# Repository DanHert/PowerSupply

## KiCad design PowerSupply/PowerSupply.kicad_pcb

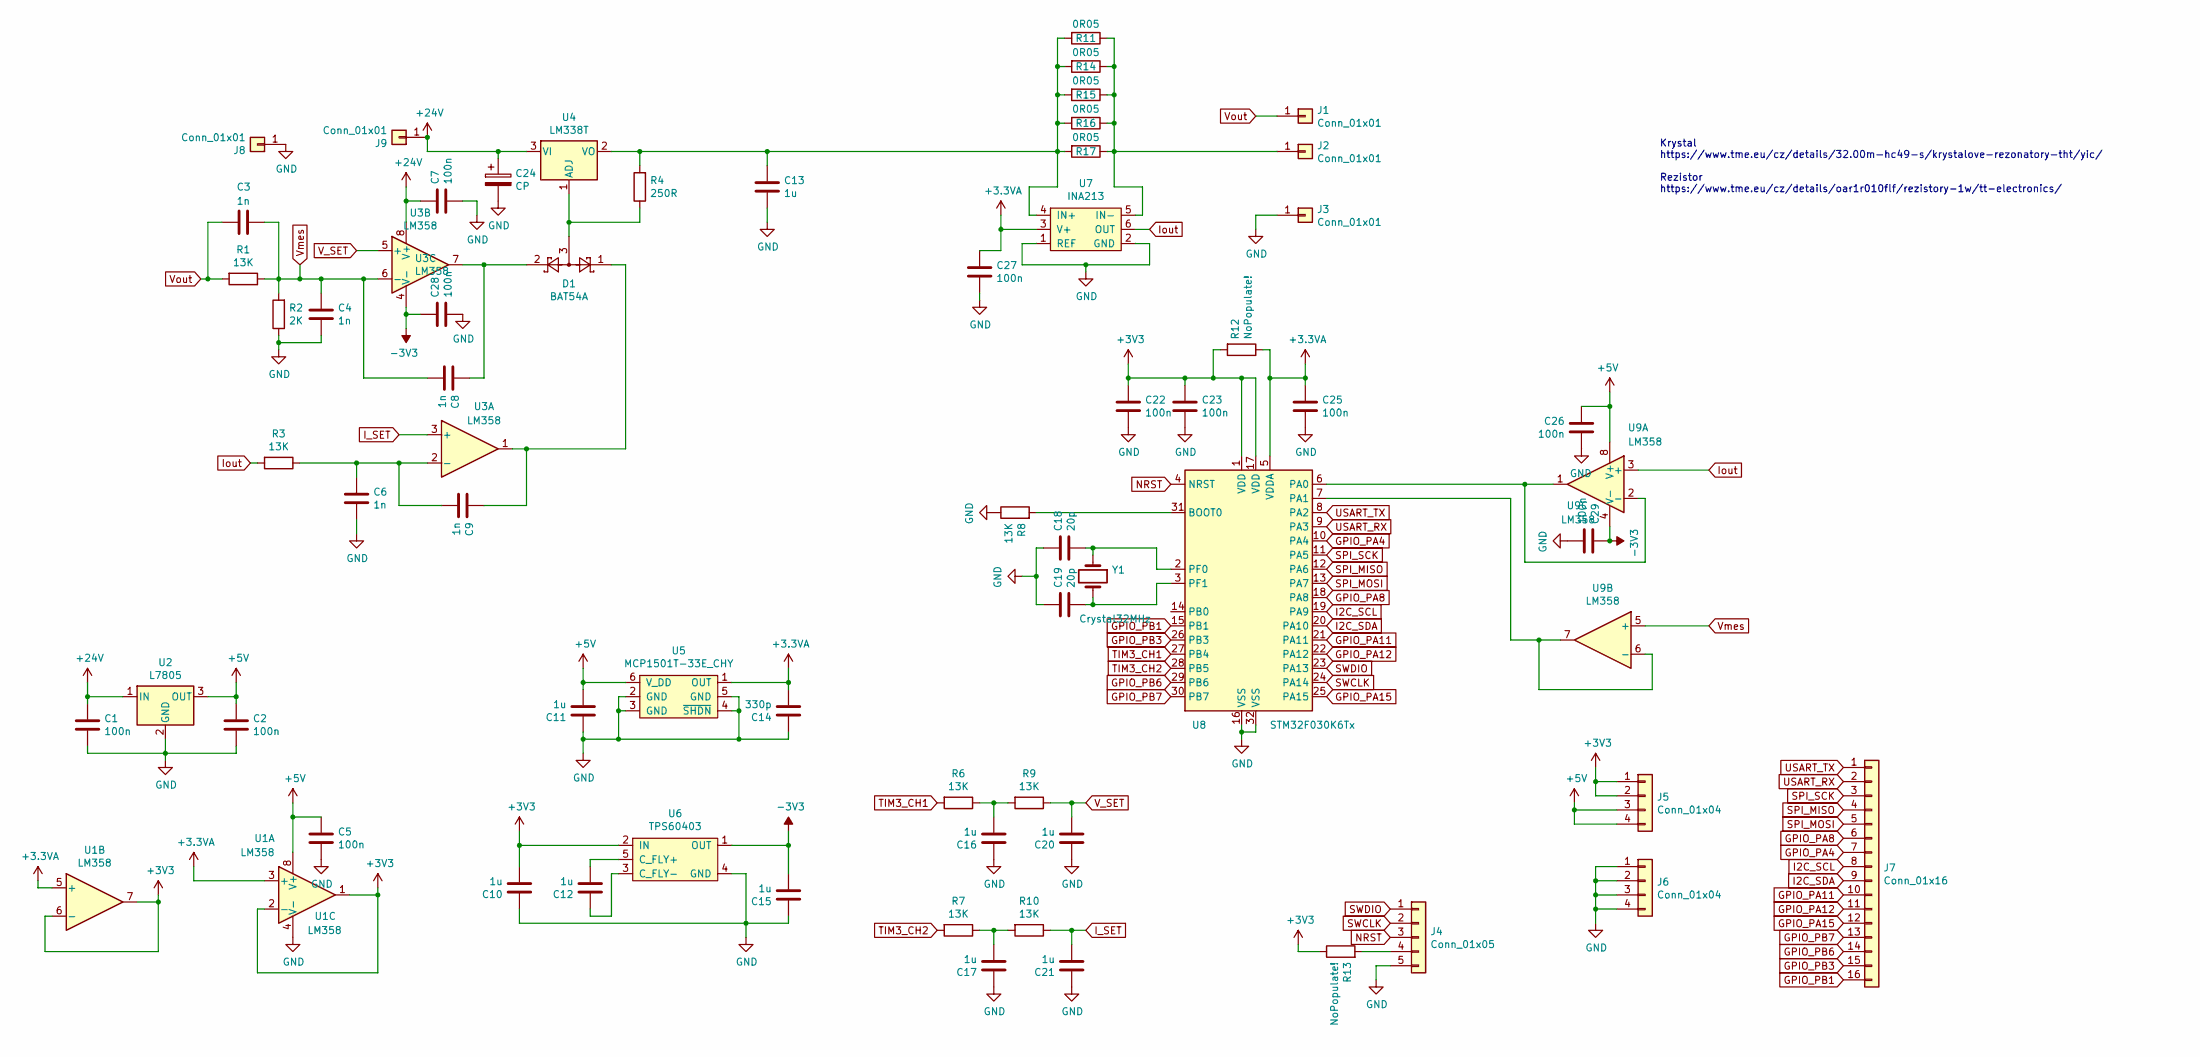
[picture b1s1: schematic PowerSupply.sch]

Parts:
C1, C2, C5, C7, C22, C23, C25, C26, C27, C28, C29: 100n; C_0805_2012Metric
C3, C4, C6, C8, C9: 1n; C_0805_2012Metric
C10, C11, C12, C13, C15, C16, C17, C20, C21: 1u; C_0805_2012Metric
C14: 330p; C_0805_2012Metric
C18, C19: 20p; C_0805_2012Metric
C24: CP; CP_Radial_D6.3mm_P2.50mm
D1: BAT54A; SOT-23
J1: Conn_01x01; SolderWirePad_1x01_Drill0.8mm
J2, J3, J8, J9: Conn_01x01; SolderWirePad_1x01_Drill2mm
J4: Conn_01x05; PinHeader_1x05_P2.54mm_Vertical
J5, J6: Conn_01x04; PinSocket_1x04_P2.54mm_Vertical
J7: Conn_01x16; PinSocket_1x16_P2.54mm_Vertical
R1, R3, R6, R7, R8, R9, R10: 13K; R_0805_2012Metric
R2: 2K; R_0805_2012Metric
R4: 250R; R_0805_2012Metric
R11, R14, R15, R16, R17: 0R05; R_1206_3216Metric
R12, R13: NoPopulate!; R_0805_2012Metric
U1, U3, U9: LM358; SOIC-8_3.9x4.9mm_P1.27mm
U2: L7805; TO-252-2
U4: LM338T; TO-220-3_Vertical
U5: MCP1501T-33E_CHY; SOT-23-6
U6: TPS60403; SOT-23-5
U7: INA213; SOT-363_SC-70-6_Handsoldering
U8: STM32F030K6Tx; LQFP-32_7x7mm_P0.8mm
Y1: Crystal32MHz; Crystal_HC49-U_Vertical

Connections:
+3.3VA: C14.2, C25.1, C27.1, R12.1, U1.3 (+), U1.5 (+), U5.1 (OUT), U7.3 (V+), U8.5 (VDDA)
+3V3: C10.2, C22.1, C23.1, J5.1, J5.2, R12.2, R13.1, U1.1, U1.2 (-), U1.6 (-), U1.7, U6.2 (IN), U8.1 (VDD), U8.17 (VDD)
+5V: C2.1, C5.1, C11.2, C26.1, J5.3, J5.4, U1.8 (V+), U2.3 (OUT), U5.6 (V_DD), U9.8 (V+)
+24V: C1.1, C7.1, C24.1, J9.1, U2.1 (IN), U3.8 (V+), U4.3 (VI)
-3V3: C15.2, C28.1, C29.1, U3.4 (V-), U6.1 (OUT), U9.4 (V-)
GND: C1.2, C2.2, C4.2, C5.2, C6.2, C7.2, C10.1, C11.1, C13.2, C14.1, C15.1, C16.1, C17.1, C18.1, C19.1, C20.1, C21.1, C22.2, C23.2, C24.2, C25.2, C26.2, C27.2, C28.2, C29.2, J3.1, J4.5, J6.1, J6.2, J6.3, J6.4, J8.1, R2.1, R8.1, U1.4 (V-), U2.2 (GND), U5.2 (GND), U5.3 (GND), U5.4 (~SHDN), U5.5 (GND), U6.4 (GND), U7.1 (REF), U7.2 (GND), U8.16 (VSS), U8.32 (VSS)
GPIO_PA4: J7.7, U8.10 (PA4)
GPIO_PA8: J7.6, U8.18 (PA8)
GPIO_PA11: J7.10, U8.21 (PA11)
GPIO_PA12: J7.11, U8.22 (PA12)
GPIO_PA15: J7.12, U8.25 (PA15)
GPIO_PB1: J7.16, U8.15 (PB1)
GPIO_PB3: J7.15, U8.26 (PB3)
GPIO_PB6: J7.14, U8.29 (PB6)
GPIO_PB7: J7.13, U8.30 (PB7)
I2C_SCL: J7.8, U8.19 (PA9)
I2C_SDA: J7.9, U8.20 (PA10)
I_SET: C21.2, R10.1, U3.3 (+)
Iout: R3.2, U7.6 (OUT), U9.3 (+)
NRST: J4.3, U8.4 (NRST)
unnamed: C6.1, C9.2, R3.1, U3.2 (-)
unnamed: C8.1, D1.2, U3.7
unnamed: C9.1, D1.1, U3.1
unnamed: C12.1, U6.3 (C_FLY-)
unnamed: C12.2, U6.5 (C_FLY+)
unnamed: C13.1, R4.2, R11.2, R14.2, R15.2, R16.2, R17.2, U4.2 (VO), U7.4 (IN+)
unnamed: C16.2, R6.1, R9.2
unnamed: C17.2, R7.1, R10.2
unnamed: C18.2, U8.2 (PF0), Y1.1
unnamed: C19.2, U8.3 (PF1), Y1.2
unnamed: D1.3, R4.1, U4.1 (ADJ)
unnamed: J2.1, R11.1, R14.1, R15.1, R16.1, R17.1, U7.5 (IN-)
unnamed: J4.4, R13.2
unnamed: R8.2, U8.31 (BOOT0)
unnamed: U8.6 (PA0), U9.1, U9.2 (-)
unnamed: U8.7 (PA1), U9.6 (-), U9.7
SPI_MISO: J7.4, U8.12 (PA6)
SPI_MOSI: J7.5, U8.13 (PA7)
SPI_SCK: J7.3, U8.11 (PA5)
SWCLK: J4.2, U8.24 (PA14)
SWDIO: J4.1, U8.23 (PA13)
TIM3_CH1: R6.2, U8.27 (PB4)
TIM3_CH2: R7.2, U8.28 (PB5)
USART_RX: J7.2, U8.9 (PA3)
USART_TX: J7.1, U8.8 (PA2)
V_SET: C20.2, R9.1, U3.5 (+)
Vmes: C3.1, C4.1, C8.2, R1.1, R2.2, U3.6 (-), U9.5 (+)
Vout: C3.2, J1.1, R1.2

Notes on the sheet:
Krystal https://www.tme.eu/cz/details/32.00m-hc49-s/krystalove-rezonatory-tht/yic/ Rezistor https://www.tme.eu/cz/details/oar1r010flf/rezistory-1w/tt-electronics/

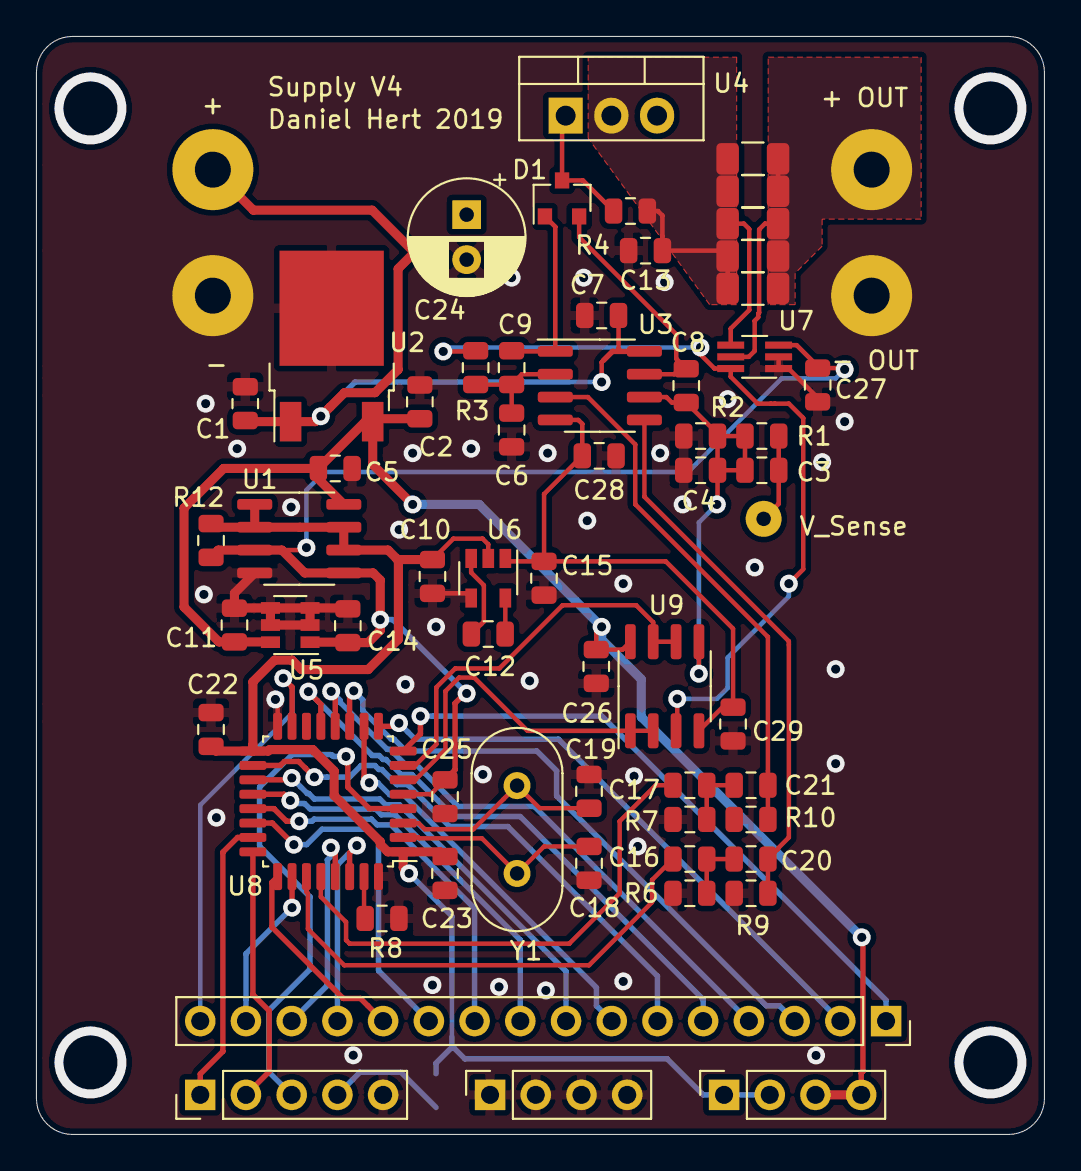
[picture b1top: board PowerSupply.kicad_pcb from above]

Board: 2 copper layers, 56.0 x 61.0 mm, 65 parts (1 on the bottom side), 48 nets.

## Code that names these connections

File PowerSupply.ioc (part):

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Mcu.Name=STM32F030K6Tx
Mcu.Package=LQFP32
Mcu.UserName=STM32F030K6Tx
PA0.Mode=IN0
PA0.Signal=ADC_IN0
PA1.Mode=IN1
PA1.Signal=ADC_IN1
PA10.Mode=I2C
PA10.Signal=I2C1_SDA
PA11.Signal=GPIO_Input
PA12.Signal=GPIO_Input
PA13.Mode=Serial_Wire
PA13.Signal=SYS_SWDIO
PA14.Mode=Serial_Wire
PA14.Signal=SYS_SWCLK
PA3.Mode=Asynchronous
PA3.Signal=USART1_RX
PA5.Mode=Full_Duplex_Master
PA5.Signal=SPI1_SCK
PA6.Mode=Full_Duplex_Master
PA6.Signal=SPI1_MISO
PA7.Mode=Full_Duplex_Master
PA7.Signal=SPI1_MOSI
PA9.Mode=Asynchronous
PA9.Signal=USART1_TX
PB0.Mode=IN8
PB0.Signal=ADC_IN8
PB4.Signal=S_TIM3_CH1
PB5.Signal=S_TIM3_CH2
PB6.Mode=I2C
PB6.Signal=I2C1_SCL
PF0-OSC_IN.Mode=HSE-External-Oscillator
PF0-OSC_IN.Signal=RCC_OSC_IN
PF1-OSC_OUT.Mode=HSE-External-Oscillator
PF1-OSC_OUT.Signal=RCC_OSC_OUT
RCC.HSE_VALUE=32000000
RCC.SYSCLKFreq_VALUE=32000000
RCC.SYSCLKSource=RCC_SYSCLKSOURCE_HSE
board=custom

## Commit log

2019-09-05 updat
2019-09-13 updaaaat
